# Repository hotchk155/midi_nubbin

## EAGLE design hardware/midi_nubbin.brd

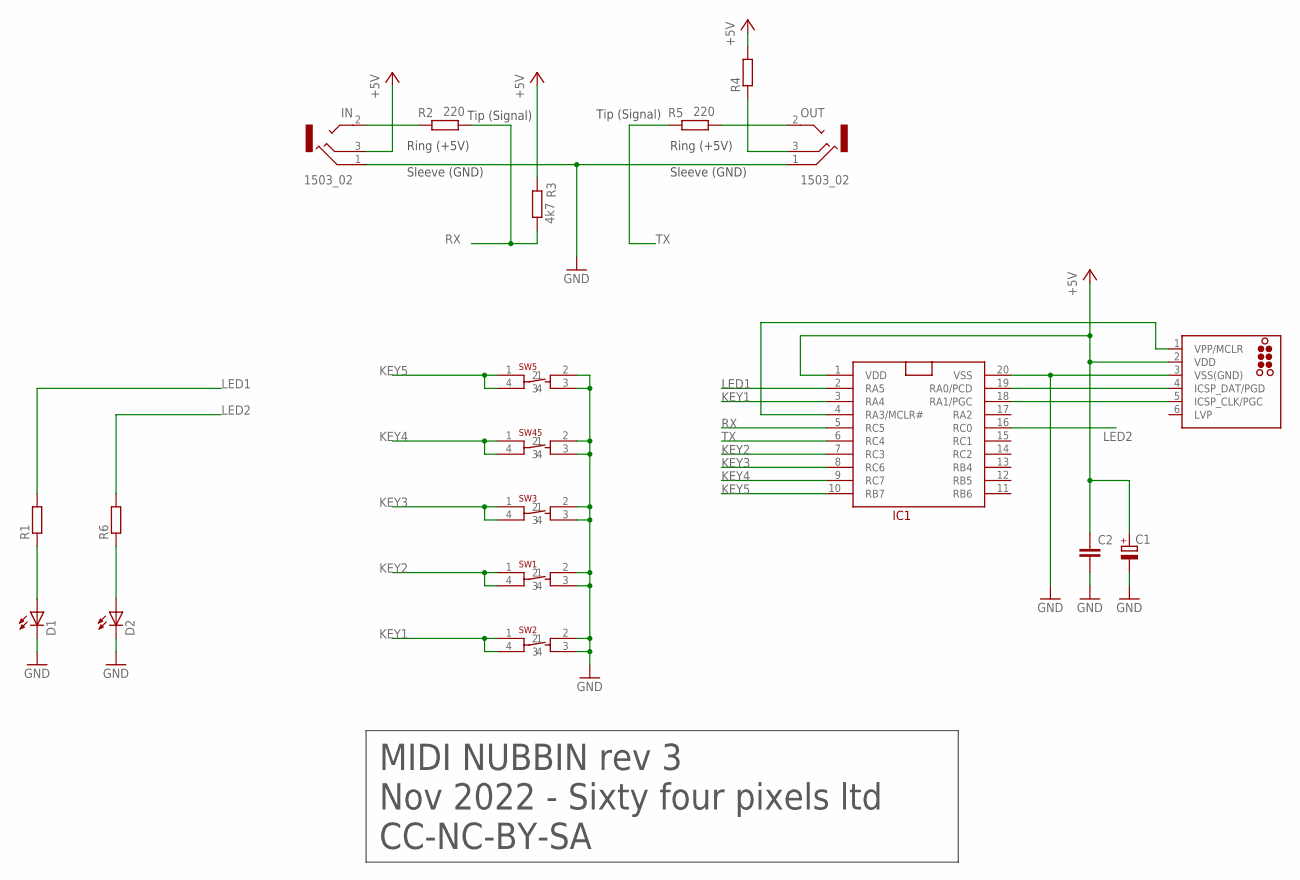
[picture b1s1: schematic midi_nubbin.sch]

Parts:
C1: CPOL-EUSMCB; SMC_B
C2: C-EUC0805; C0805
D1, D2: LEDCHIPLED_0805; CHIPLED_0805
IC1: PIC16F15345SSOP20; SSOP20
ICSP: TC2030-MCP-NL
IN: 1503_02
OUT: 1503_02
R1, R4, R6: R-EU_R0805; R0805
R2, R5: 220; R0805
R3: 4k7; R0805
SW1, SW2, SW3, SW5, SW45: 6MMTACTSMT

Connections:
+5V: C1.+, C2.1, IC1.1 (VDD), ICSP.2 (VDD), IN.3, R3.2, R4.2
GND: C1.-, C2.2, D1.C, D2.C, IC1.20 (VSS), ICSP.3 (VSS(GND)), IN.1, OUT.1, SW1.2, SW1.3, SW2.2, SW2.3, SW3.2, SW3.3, SW5.2, SW5.3, SW45.2, SW45.3
KEY1: IC1.3 (RA4), SW2.1, SW2.4
KEY2: IC1.7 (RC3), SW1.1, SW1.4
KEY3: IC1.8 (RC6), SW3.1, SW3.4
KEY4: IC1.9 (RC7), SW45.1, SW45.4
KEY5: IC1.10 (RB7), SW5.1, SW5.4
LED1: IC1.2 (RA5), R1.2
LED2: IC1.16 (RC0), R6.2
unnamed: D1.A, R1.1
unnamed: D2.A, R6.1
unnamed: OUT.3, R4.1
unnamed: OUT.2, R5.1
unnamed: IN.2, R2.2
PGC: IC1.18 (RA1/PGC), ICSP.5 (ICSP_CLK/PGC)
PGD: IC1.19 (RA0/PCD), ICSP.4 (ICSP_DAT/PGD)
RX: IC1.5 (RC5), R2.1, R3.1
TX: IC1.6 (RC4), R5.2
VPP: IC1.4 (RA3/MCLR#), ICSP.1 (VPP/MCLR)

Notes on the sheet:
MIDI NUBBIN rev 3
Nov 2022 - Sixty four pixels ltd
CC-NC-BY-SA
Tip (Signal)
Ring (+5V)
Sleeve (GND)

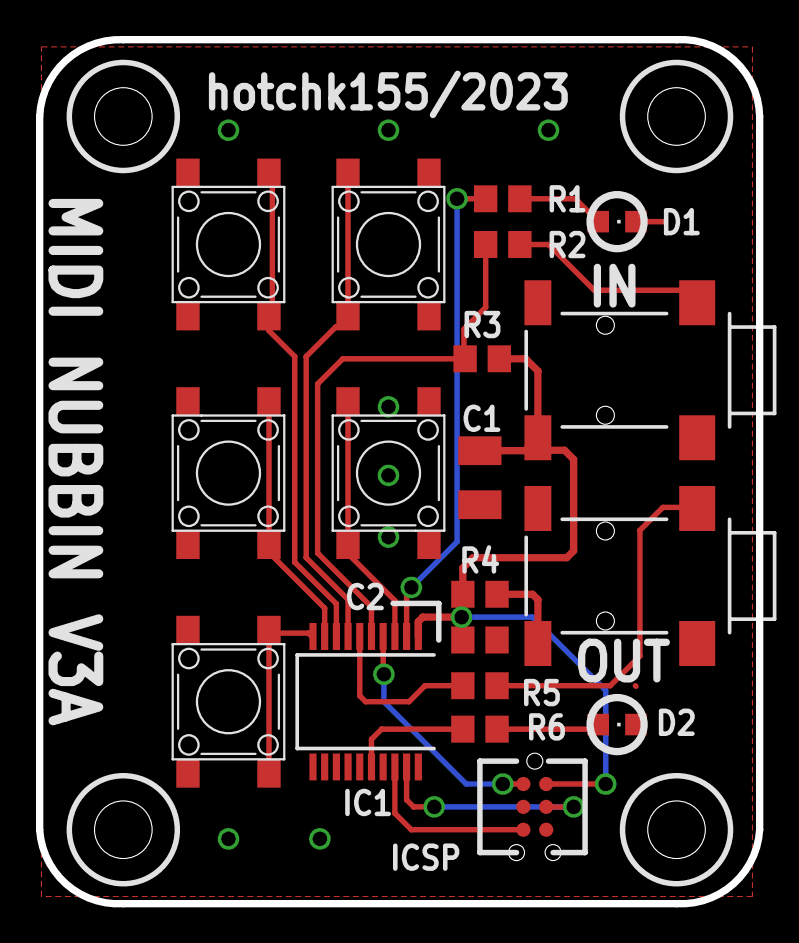
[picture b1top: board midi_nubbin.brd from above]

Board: 2 copper layers, 40.0 x 48.0 mm, 19 parts (0 on the bottom side), 19 nets.

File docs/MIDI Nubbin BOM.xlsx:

Reflow
C1 | 10u | Tantalum Cap SMCB
C2 | 100n | Ceramic Cap 0805
D1, D2 | Blue LED | LED 0805
IC1 | PIC16F15345-I/SS | Microcontroller TSSOP20
R1, R6 | 1K | 0805 Resistor
R2, R4, R5 | 220R | 0805 Resistor
R3 | 4k7 | 0805 Resistor
Manually soldered
5 OFF | DTSM-65N-V-B | 6x6x9.5mm Tact Switch SMT
2 OFF | LUMBERG 1503 02 | Stereo 3.5mm jack SMT

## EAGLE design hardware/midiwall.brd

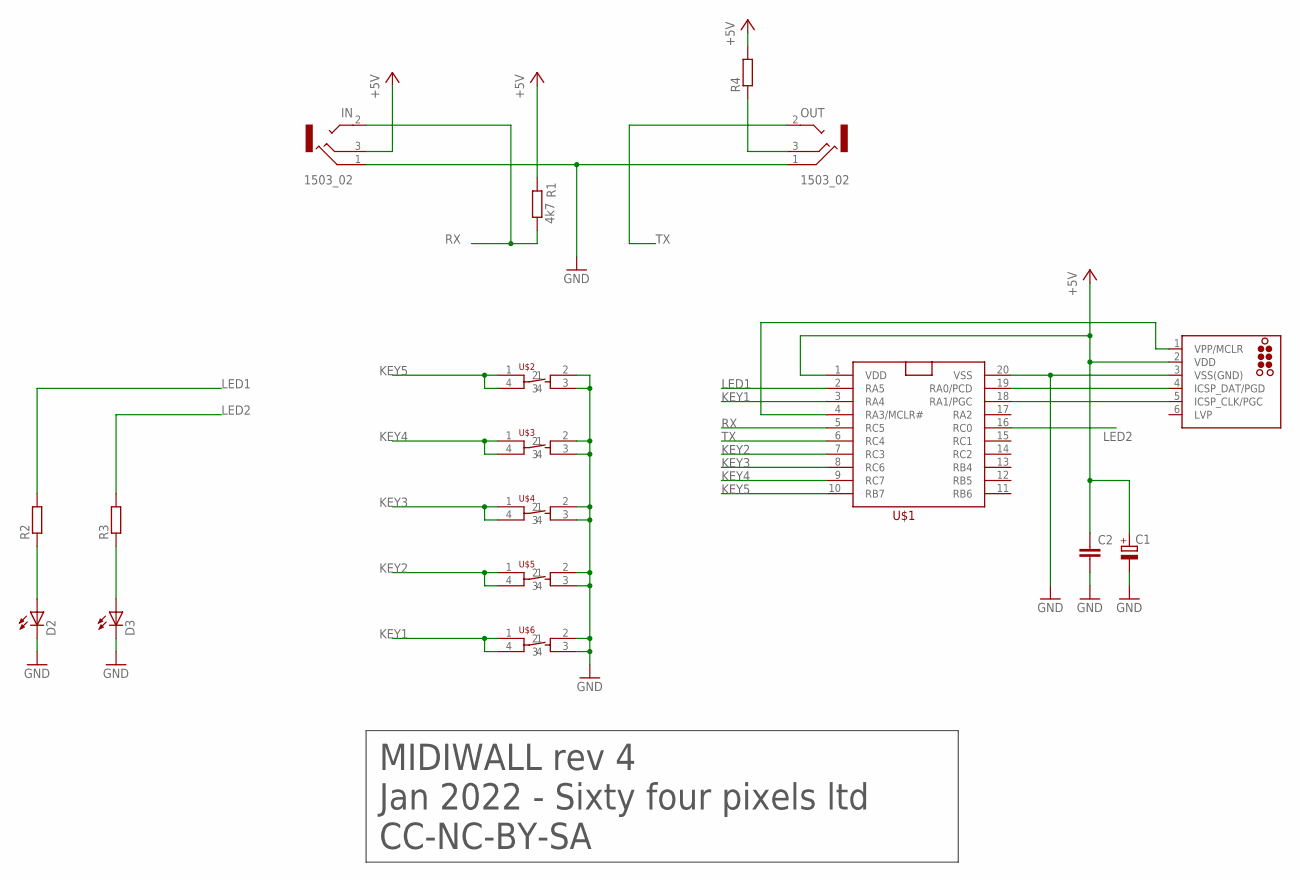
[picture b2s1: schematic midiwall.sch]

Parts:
C1: CPOL-EUSMCB; SMC_B
C2: C-EUC0805; C0805
D2, D3: LEDCHIPLED_0805; CHIPLED_0805
ICSP: TC2030-MCP-NL
IN: 1503_02
OUT: 1503_02
R1: 4k7; R0805
R2, R3, R4: R-EU_R0805; R0805
U$1: PIC16F15345; TSSOP20
U$2, U$3, U$4, U$5, U$6: 6MMTACTSMT

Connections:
+5V: C1.+, C2.1, ICSP.2 (VDD), IN.3, R1.2, R4.2, U$1.1 (VDD)
GND: C1.-, C2.2, D2.C, D3.C, ICSP.3 (VSS(GND)), IN.1, OUT.1, U$1.20 (VSS), U$2.2, U$2.3, U$3.2, U$3.3, U$4.2, U$4.3, U$5.2, U$5.3, U$6.2, U$6.3
KEY1: U$1.3 (RA4), U$6.1, U$6.4
KEY2: U$1.7 (RC3), U$5.1, U$5.4
KEY3: U$1.8 (RC6), U$4.1, U$4.4
KEY4: U$1.9 (RC7), U$3.1, U$3.4
KEY5: U$1.10 (RB7), U$2.1, U$2.4
LED1: R2.2, U$1.2 (RA5)
LED2: R3.2, U$1.16 (RC0)
unnamed: D2.A, R2.1
unnamed: D3.A, R3.1
unnamed: OUT.3, R4.1
PGC: ICSP.5 (ICSP_CLK/PGC), U$1.18 (RA1/PGC)
PGD: ICSP.4 (ICSP_DAT/PGD), U$1.19 (RA0/PCD)
RX: IN.2, R1.1, U$1.5 (RC5)
TX: OUT.2, U$1.6 (RC4)
VPP: ICSP.1 (VPP/MCLR), U$1.4 (RA3/MCLR#)

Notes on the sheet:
MIDIWALL rev 4
Jan 2022 - Sixty four pixels ltd
CC-NC-BY-SA

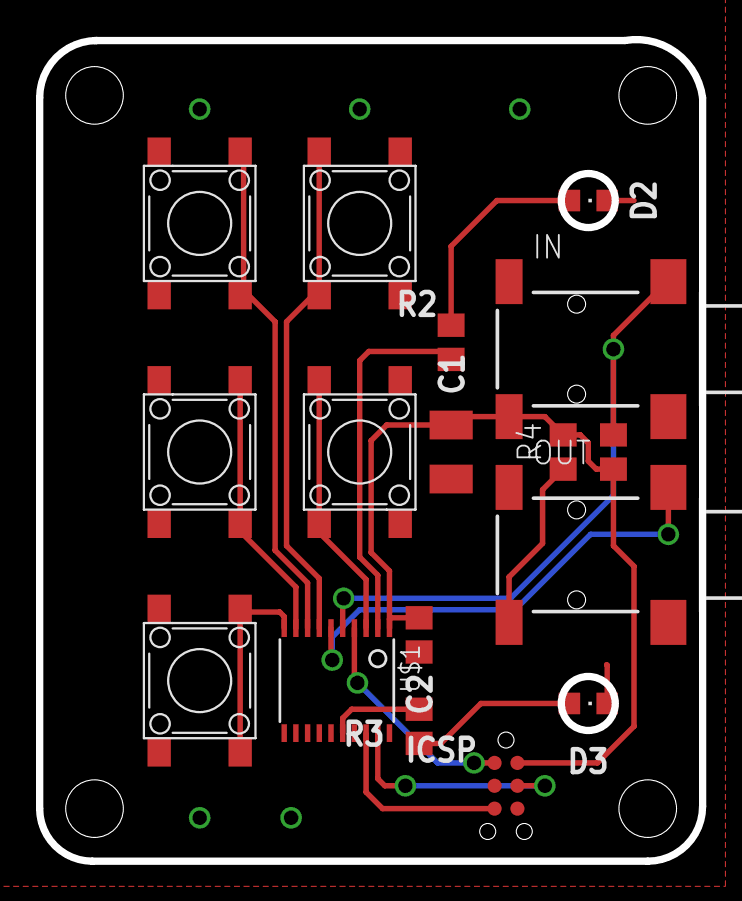
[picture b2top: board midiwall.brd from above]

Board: 2 copper layers, 36.8 x 45.6 mm, 17 parts (0 on the bottom side), 17 nets.

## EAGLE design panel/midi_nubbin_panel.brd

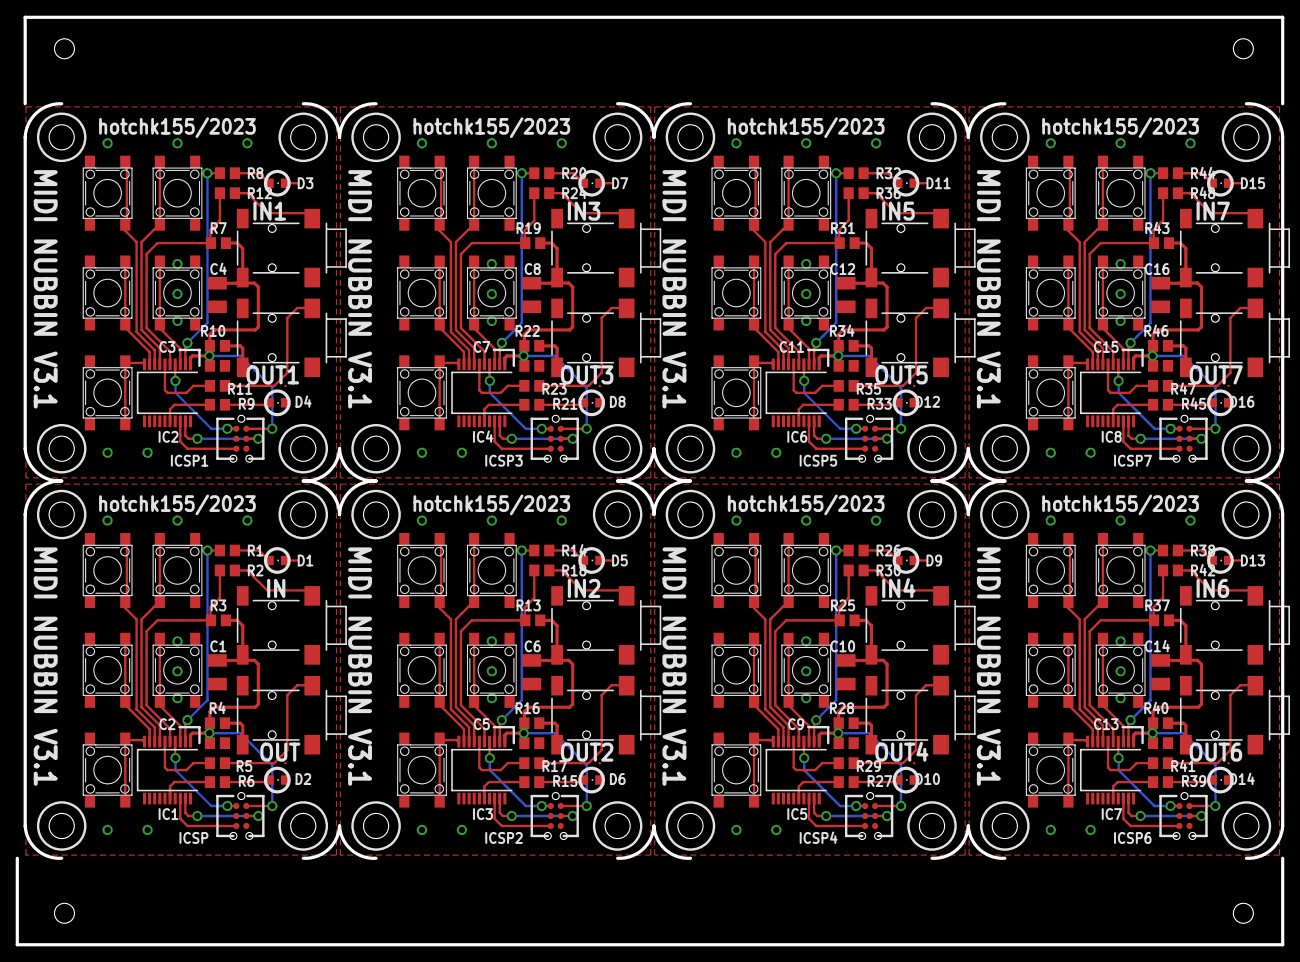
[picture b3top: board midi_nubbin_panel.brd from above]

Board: 2 copper layers, 161.0 x 118.0 mm, 152 parts (0 on the bottom side), 152 nets.

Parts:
C1, C4, C6, C8, C10, C12, C14, C16: SMC_B
C2, C3, C5, C7, C9, C11, C13, C15: C0805
D1, D2, D3, D4, D5, D6, D7, D8, D9, D10, D11, D12, D13, D14, D15, D16: CHIPLED_0805
IC1, IC2, IC3, IC4, IC5, IC6, IC7, IC8: PIC16F15345SSOP20; SSOP20
ICSP, ICSP1, ICSP2, ICSP3, ICSP4, ICSP5, ICSP6, ICSP7: TC2030-MCP-NL
IN, IN1, IN2, IN3, IN4, IN5, IN6, IN7: 1503_02
OUT, OUT1, OUT2, OUT3, OUT4, OUT5, OUT6, OUT7: 1503_02
R1, R4, R6, R8, R9, R10, R14, R15, R16, R20, R21, R22, R26, R27, R28, R32, R33, R34, R38, R39, R40, R44, R45, R46: R0805
R2, R5, R11, R12, R17, R18, R23, R24, R29, R30, R35, R36, R41, R42, R47, R48: 220; R0805
R3, R7, R13, R19, R25, R31, R37, R43: 4k7; R0805
SW1, SW2, SW3, SW4, SW5, SW6, SW7, SW8, SW9, SW10, SW11, SW12, SW13, SW14, SW15, SW16, SW17, SW18, SW19, SW20, SW21, SW22, SW23, SW24, SW25, SW26, SW27, SW28, SW29, SW30, SW31, SW32, SW33, SW34, SW35, SW36, SW37, SW38, SW39, SW45: 6MMTACTSMT

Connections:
+5V: C1.+, C2.1, IC1.1, ICSP.2, IN.3, R3.2, R4.2
+5V1: C3.1, C4.+, IC2.1, ICSP1.2, IN1.3, R7.2, R10.2
+5V2: C5.1, C6.+, IC3.1, ICSP2.2, IN2.3, R13.2, R16.2
+5V3: C7.1, C8.+, IC4.1, ICSP3.2, IN3.3, R19.2, R22.2
+5V4: C9.1, C10.+, IC5.1, ICSP4.2, IN4.3, R25.2, R28.2
+5V5: C11.1, C12.+, IC6.1, ICSP5.2, IN5.3, R31.2, R34.2
+5V6: C13.1, C14.+, IC7.1, ICSP6.2, IN6.3, R37.2, R40.2
+5V7: C15.1, C16.+, IC8.1, ICSP7.2, IN7.3, R43.2, R46.2
GND: C1.-, C2.2, D1.C, D2.C, IC1.20, ICSP.3, IN.1, OUT.1, SW1.2, SW1.3, SW2.2, SW2.3, SW3.2, SW3.3, SW5.2, SW5.3, SW45.2, SW45.3
GND1: C3.2, C4.-, D3.C, D4.C, IC2.20, ICSP1.3, IN1.1, OUT1.1, SW4.2, SW4.3, SW6.2, SW6.3, SW7.2, SW7.3, SW8.2, SW8.3, SW9.2, SW9.3
GND2: C5.2, C6.-, D5.C, D6.C, IC3.20, ICSP2.3, IN2.1, OUT2.1, SW10.2, SW10.3, SW11.2, SW11.3, SW12.2, SW12.3, SW13.2, SW13.3, SW14.2, SW14.3
GND3: C7.2, C8.-, D7.C, D8.C, IC4.20, ICSP3.3, IN3.1, OUT3.1, SW15.2, SW15.3, SW16.2, SW16.3, SW17.2, SW17.3, SW18.2, SW18.3, SW19.2, SW19.3
GND4: C9.2, C10.-, D9.C, D10.C, IC5.20, ICSP4.3, IN4.1, OUT4.1, SW20.2, SW20.3, SW21.2, SW21.3, SW22.2, SW22.3, SW23.2, SW23.3, SW24.2, SW24.3
GND5: C11.2, C12.-, D11.C, D12.C, IC6.20, ICSP5.3, IN5.1, OUT5.1, SW25.2, SW25.3, SW26.2, SW26.3, SW27.2, SW27.3, SW28.2, SW28.3, SW29.2, SW29.3
GND6: C13.2, C14.-, D13.C, D14.C, IC7.20, ICSP6.3, IN6.1, OUT6.1, SW30.2, SW30.3, SW31.2, SW31.3, SW32.2, SW32.3, SW33.2, SW33.3, SW34.2, SW34.3
GND7: C15.2, C16.-, D15.C, D16.C, IC8.20, ICSP7.3, IN7.1, OUT7.1, SW35.2, SW35.3, SW36.2, SW36.3, SW37.2, SW37.3, SW38.2, SW38.3, SW39.2, SW39.3
KEY1: IC1.3, SW2.1, SW2.4
KEY2: IC1.7, SW1.1, SW1.4
KEY3: IC1.8, SW3.1, SW3.4
KEY4: IC1.9, SW45.1, SW45.4
KEY5: IC1.10, SW5.1, SW5.4
KEY6: IC2.8, SW7.1, SW7.4
KEY7: IC2.3, SW9.1, SW9.4
KEY8: IC2.7, SW8.1, SW8.4
KEY9: IC2.9, SW6.1, SW6.4
KEY10: IC2.10, SW4.1, SW4.4
KEY11: IC3.8, SW12.1, SW12.4
KEY12: IC3.3, SW14.1, SW14.4
KEY13: IC3.7, SW13.1, SW13.4
KEY14: IC3.9, SW11.1, SW11.4
KEY15: IC3.10, SW10.1, SW10.4
KEY16: IC4.8, SW17.1, SW17.4
KEY17: IC4.3, SW19.1, SW19.4
KEY18: IC4.7, SW18.1, SW18.4
KEY19: IC4.9, SW16.1, SW16.4
KEY20: IC4.10, SW15.1, SW15.4
KEY21: IC5.8, SW22.1, SW22.4
KEY22: IC5.3, SW24.1, SW24.4
KEY23: IC5.7, SW23.1, SW23.4
KEY24: IC5.9, SW21.1, SW21.4
KEY25: IC5.10, SW20.1, SW20.4
KEY26: IC6.8, SW27.1, SW27.4
KEY27: IC6.3, SW29.1, SW29.4
KEY28: IC6.7, SW28.1, SW28.4
KEY29: IC6.9, SW26.1, SW26.4
KEY30: IC6.10, SW25.1, SW25.4
KEY31: IC7.8, SW32.1, SW32.4
KEY32: IC7.3, SW34.1, SW34.4
KEY33: IC7.7, SW33.1, SW33.4
KEY34: IC7.9, SW31.1, SW31.4
KEY35: IC7.10, SW30.1, SW30.4
KEY36: IC8.8, SW37.1, SW37.4
KEY37: IC8.3, SW39.1, SW39.4
KEY38: IC8.7, SW38.1, SW38.4
KEY39: IC8.9, SW36.1, SW36.4
KEY40: IC8.10, SW35.1, SW35.4
LED1: IC1.2, R1.2
LED2: IC1.16, R6.2
LED3: IC2.2, R8.2
LED4: IC2.16, R9.2
LED5: IC3.2, R14.2
LED6: IC3.16, R15.2
LED7: IC4.2, R20.2
LED8: IC4.16, R21.2
LED9: IC5.2, R26.2
LED10: IC5.16, R27.2
LED11: IC6.2, R32.2
LED12: IC6.16, R33.2
LED13: IC7.2, R38.2
LED14: IC7.16, R39.2
LED15: IC8.2, R44.2
LED16: IC8.16, R45.2
unnamed: D1.A, R1.1
unnamed: D2.A, R6.1
unnamed: OUT.3, R4.1
unnamed: OUT.2, R5.1
unnamed: IN.2, R2.2
unnamed: D3.A, R8.1
unnamed: D4.A, R9.1
unnamed: OUT1.3, R10.1
unnamed: OUT1.2, R11.1
unnamed: IN1.2, R12.2
unnamed: D5.A, R14.1
unnamed: D6.A, R15.1
unnamed: OUT2.3, R16.1
unnamed: OUT2.2, R17.1
unnamed: IN2.2, R18.2
unnamed: D7.A, R20.1
unnamed: D8.A, R21.1
unnamed: OUT3.3, R22.1
unnamed: OUT3.2, R23.1
unnamed: IN3.2, R24.2
unnamed: D9.A, R26.1
unnamed: D10.A, R27.1
unnamed: OUT4.3, R28.1
unnamed: OUT4.2, R29.1
unnamed: IN4.2, R30.2
unnamed: D11.A, R32.1
unnamed: D12.A, R33.1
unnamed: OUT5.3, R34.1
unnamed: OUT5.2, R35.1
unnamed: IN5.2, R36.2
unnamed: D13.A, R38.1
unnamed: D14.A, R39.1
unnamed: OUT6.3, R40.1
unnamed: OUT6.2, R41.1
unnamed: IN6.2, R42.2
unnamed: D15.A, R44.1
unnamed: D16.A, R45.1
unnamed: OUT7.3, R46.1
unnamed: OUT7.2, R47.1
unnamed: IN7.2, R48.2
PGC: IC1.18, ICSP.5
PGC1: IC2.18, ICSP1.5
PGC2: IC3.18, ICSP2.5
PGC3: IC4.18, ICSP3.5
PGC4: IC5.18, ICSP4.5
PGC5: IC6.18, ICSP5.5
PGC6: IC7.18, ICSP6.5
PGC7: IC8.18, ICSP7.5
PGD: IC1.19, ICSP.4
PGD1: IC2.19, ICSP1.4
PGD2: IC3.19, ICSP2.4
PGD3: IC4.19, ICSP3.4
PGD4: IC5.19, ICSP4.4
PGD5: IC6.19, ICSP5.4
PGD6: IC7.19, ICSP6.4
PGD7: IC8.19, ICSP7.4
RX: IC1.5, R2.1, R3.1
RX1: IC2.5, R7.1, R12.1
RX2: IC3.5, R13.1, R18.1
RX3: IC4.5, R19.1, R24.1
RX4: IC5.5, R25.1, R30.1
RX5: IC6.5, R31.1, R36.1
RX6: IC7.5, R37.1, R42.1
RX7: IC8.5, R43.1, R48.1
TX: IC1.6, R5.2
TX1: IC2.6, R11.2
TX2: IC3.6, R17.2
TX3: IC4.6, R23.2
TX4: IC5.6, R29.2
TX5: IC6.6, R35.2
TX6: IC7.6, R41.2
TX7: IC8.6, R47.2
VPP: IC1.4, ICSP.1
VPP1: IC2.4, ICSP1.1
VPP2: IC3.4, ICSP2.1
VPP3: IC4.4, ICSP3.1
VPP4: IC5.4, ICSP4.1
VPP5: IC6.4, ICSP5.1
VPP6: IC7.4, ICSP6.1
VPP7: IC8.4, ICSP7.1

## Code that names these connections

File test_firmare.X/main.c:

// PIC16F15345 Configuration Bit Settings
// 'C' source line config statements
// CONFIG1
#pragma config FEXTOSC = OFF    // External Oscillator mode selection bits (Oscillator not enabled)
#pragma config RSTOSC = HFINTPLL// Power-up default value for COSC bits (HFINTOSC with 2x PLL, with OSCFRQ = 16 MHz and CDIV = 1:1 (FOSC = 32 MHz))
#pragma config CLKOUTEN = OFF   // Clock Out Enable bit (CLKOUT function is disabled; i/o or oscillator function on OSC2)
#pragma config CSWEN = ON       // Clock Switch Enable bit (Writing to NOSC and NDIV is allowed)
#pragma config FCMEN = ON       // Fail-Safe Clock Monitor Enable bit (FSCM timer enabled)

// CONFIG2
#pragma config MCLRE = OFF      // Master Clear Enable bit (MCLR pin function is port defined function)
#pragma config PWRTE = OFF      // Power-up Timer Enable bit (PWRT disabled)
#pragma config LPBOREN = OFF    // Low-Power BOR enable bit (ULPBOR disabled)
#pragma config BOREN = ON       // Brown-out reset enable bits (Brown-out Reset Enabled, SBOREN bit is ignored)
#pragma config BORV = LO        // Brown-out Reset Voltage Selection (Brown-out Reset Voltage (VBOR) set to 1.9V on LF, and 2.45V on F Devices)
#pragma config ZCD = OFF        // Zero-cross detect disable (Zero-cross detect circuit is disabled at POR.)
#pragma config PPS1WAY = ON     // Peripheral Pin Select one-way control (The PPSLOCK bit can be cleared and set only once in software)
#pragma config STVREN = ON      // Stack Overflow/Underflow Reset Enable bit (Stack Overflow or Underflow will cause a reset)

// CONFIG3
#pragma config WDTCPS = WDTCPS_31// WDT Period Select bits (Divider ratio 1:65536; software control of WDTPS)
#pragma config WDTE = OFF        // WDT operating mode (WDT enabled regardless of sleep; SWDTEN ignored)
#pragma config WDTCWS = WDTCWS_7// WDT Window Select bits (window always open (100%); software control; keyed access not required)
#pragma config WDTCCS = SC      // WDT input clock selector (Software Control)

// CONFIG4
#pragma config BBSIZE = BB512   // Boot Block Size Selection bits (512 words boot block size)
#pragma config BBEN = OFF       // Boot Block Enable bit (Boot Block disabled)
#pragma config SAFEN = ON       // SAF Enable bit 
#pragma config WRTAPP = OFF     // Application Block Write Protection bit (Application Block not write protected)
#pragma config WRTB = OFF       // Boot Block Write Protection bit (Boot Block not write protected)
#pragma config WRTC = OFF       // Configuration Register Write Protection bit (Configuration Register not write protected)
#pragma config WRTSAF = OFF     // Storage Area Flash Write Protection bit (SAF not write protected)
#pragma config LVP = OFF        // Low Voltage Programming Enable bit (High Voltage on MCLR/Vpp must be used for programming)

// CONFIG5
#pragma config CP = OFF         // UserNVM Program memory code protection bit (UserNVM code protection disabled)

// #pragma config statements should precede project file includes.
// Use project enums instead of #define for ON and OFF.

#include <xc.h>
#define P_LED1 LATAbits.LATA5
#define P_LED2 LATCbits.LATC0
#define P_KEY1 PORTCbits.RC3
#define P_KEY2 PORTAbits.RA4
#define P_KEY3 PORTCbits.RC6
#define P_KEY4 PORTCbits.RC7
#define P_KEY5 PORTBbits.RB7

#define TRISA_BITS  0b11011111
#define TRISB_BITS  0b11111111
#define TRISC_BITS  0b11101110

#define WPUA_BITS   0b00010000
#define WPUB_BITS   0b10000000
#define WPUC_BITS   0b11001000

#define DEBOUNCE_TIMEOUT 50
#define LONG_PRESS_TIMEOUT 1000
#define LED_BLINK_MS 100

#define _XTAL_FREQ 32000000

//////////////////////////////////////////
void uart_init() {
     
    TX1STAbits.TX9 = 0;     // 8 bit transmission
    TX1STAbits.TXEN = 1;    // transmit enable    
    TX1STAbits.SYNC = 0;    // async mode
    TX1STAbits.SENDB = 0;   // break character
    TX1STAbits.BRGH = 0;    // low baudrate 
    
    RC1STAbits.RX9 = 0;     // 8 bit operation
    RC1STAbits.CREN = 0;    // continuous receive enable

    BAUD1CONbits.SCKP = 0;  // bit polarity 
    BAUD1CONbits.BRG16 = 1; // enable 16 bit brg
    BAUD1CONbits.WUE = 0;   // wake up enable off
    BAUD1CONbits.ABDEN = 0; // auto baud detect

    SP1BRGH = 0;            // brg high byte
    SP1BRGL = 63;            // brg low byte (31250)	 

    RC1STAbits.SPEN = 1;    // serial port enable    
    
    PIR3bits.RC1IF = 0;     
    PIE3bits.RC1IE = 0;     

    PIR3bits.TX1IF = 0;     
    PIE3bits.TX1IE = 0;     // only enabled when sending
}
void uart_send(unsigned char ch) 
{
	TXREG = ch;
	while(!TXSTAbits.TRMT);
}

///////////////////////////////////////////////////
void main() {

    TRISA=TRISA_BITS;
    TRISB=TRISB_BITS;
    TRISC=TRISC_BITS;
    ANSELA = 0;
    ANSELB = 0;
    ANSELC = 0;
    WPUA=WPUA_BITS;
    WPUB=WPUB_BITS;
    WPUC=WPUC_BITS;
    PORTA=0;  
    PORTC=0;  
    
    // Pin RC4 PPS register set to point to UART TX
    RC4PPS = 0x0F;
    
    // UART RX PPS register set to point to RC5
    RX1DTPPS = 0x15;
    
    uart_init();
    int sent = 0;
    while(1) {
        P_LED1 = 1;
        P_LED2 = 0;
        __delay_ms(200);
        P_LED1 = 0;
        P_LED2 = 1;
        __delay_ms(200);
        while(!P_KEY1 || !P_KEY2 || !P_KEY3 || !P_KEY4 || !P_KEY5 ) {
            P_LED1 = 1;
            P_LED2 = 1;                      
            if(!sent) {
                if(!P_KEY1) sent=36;
                else if(!P_KEY2) sent=38;
                else if(!P_KEY3) sent=40;
                else if(!P_KEY4) sent=41;
                else if(!P_KEY5) sent=43;                
                uart_send(0x90);
                uart_send(sent);
                uart_send(127);
            }            
        }
        if(sent) {
            uart_send(0x90);
            uart_send(sent);
            uart_send(0);
            sent = 0;
        }
        
    }
}

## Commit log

2019-05-16 s
    s
2019-06-30 v2 poss
2019-07-24 test
2019-09-30 new case
2019-10-08 REV3
2022-01-11 Version 4 PCB PROD
2022-04-05 assdadasadsaddas
2022-04-06 MN V1 PCB?
2022-08-08 Change SSOP footprint
2022-08-08 BOARD V2
2022-10-07 mcu change
2022-11-25 add logo
2022-11-25 panelize, stencil, fascia
2022-11-25 checkin
2023-05-03 V3.1 increase min via hole size
2023-05-03 panelised 3.1
2024-10-02 dsfdsff
2024-10-09 sdfdsfdf
2024-10-10 sdsds
2024-10-15 sadds
2024-10-16 dsfsdf
2024-10-17 asdas
2024-10-25 add generic fasica
2024-10-25 adding generic fascia
2024-11-18 fascia v2
2024-12-05 add test firmware
2024-12-10 test firmware
2024-12-11 refactoring
2025-04-09 work in progress

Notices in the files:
parts and their libraries:
tag-connect: ©2009 ROFA.cz - modified and updated by Robert Darlington ‹rdarlington@gmail.com›
